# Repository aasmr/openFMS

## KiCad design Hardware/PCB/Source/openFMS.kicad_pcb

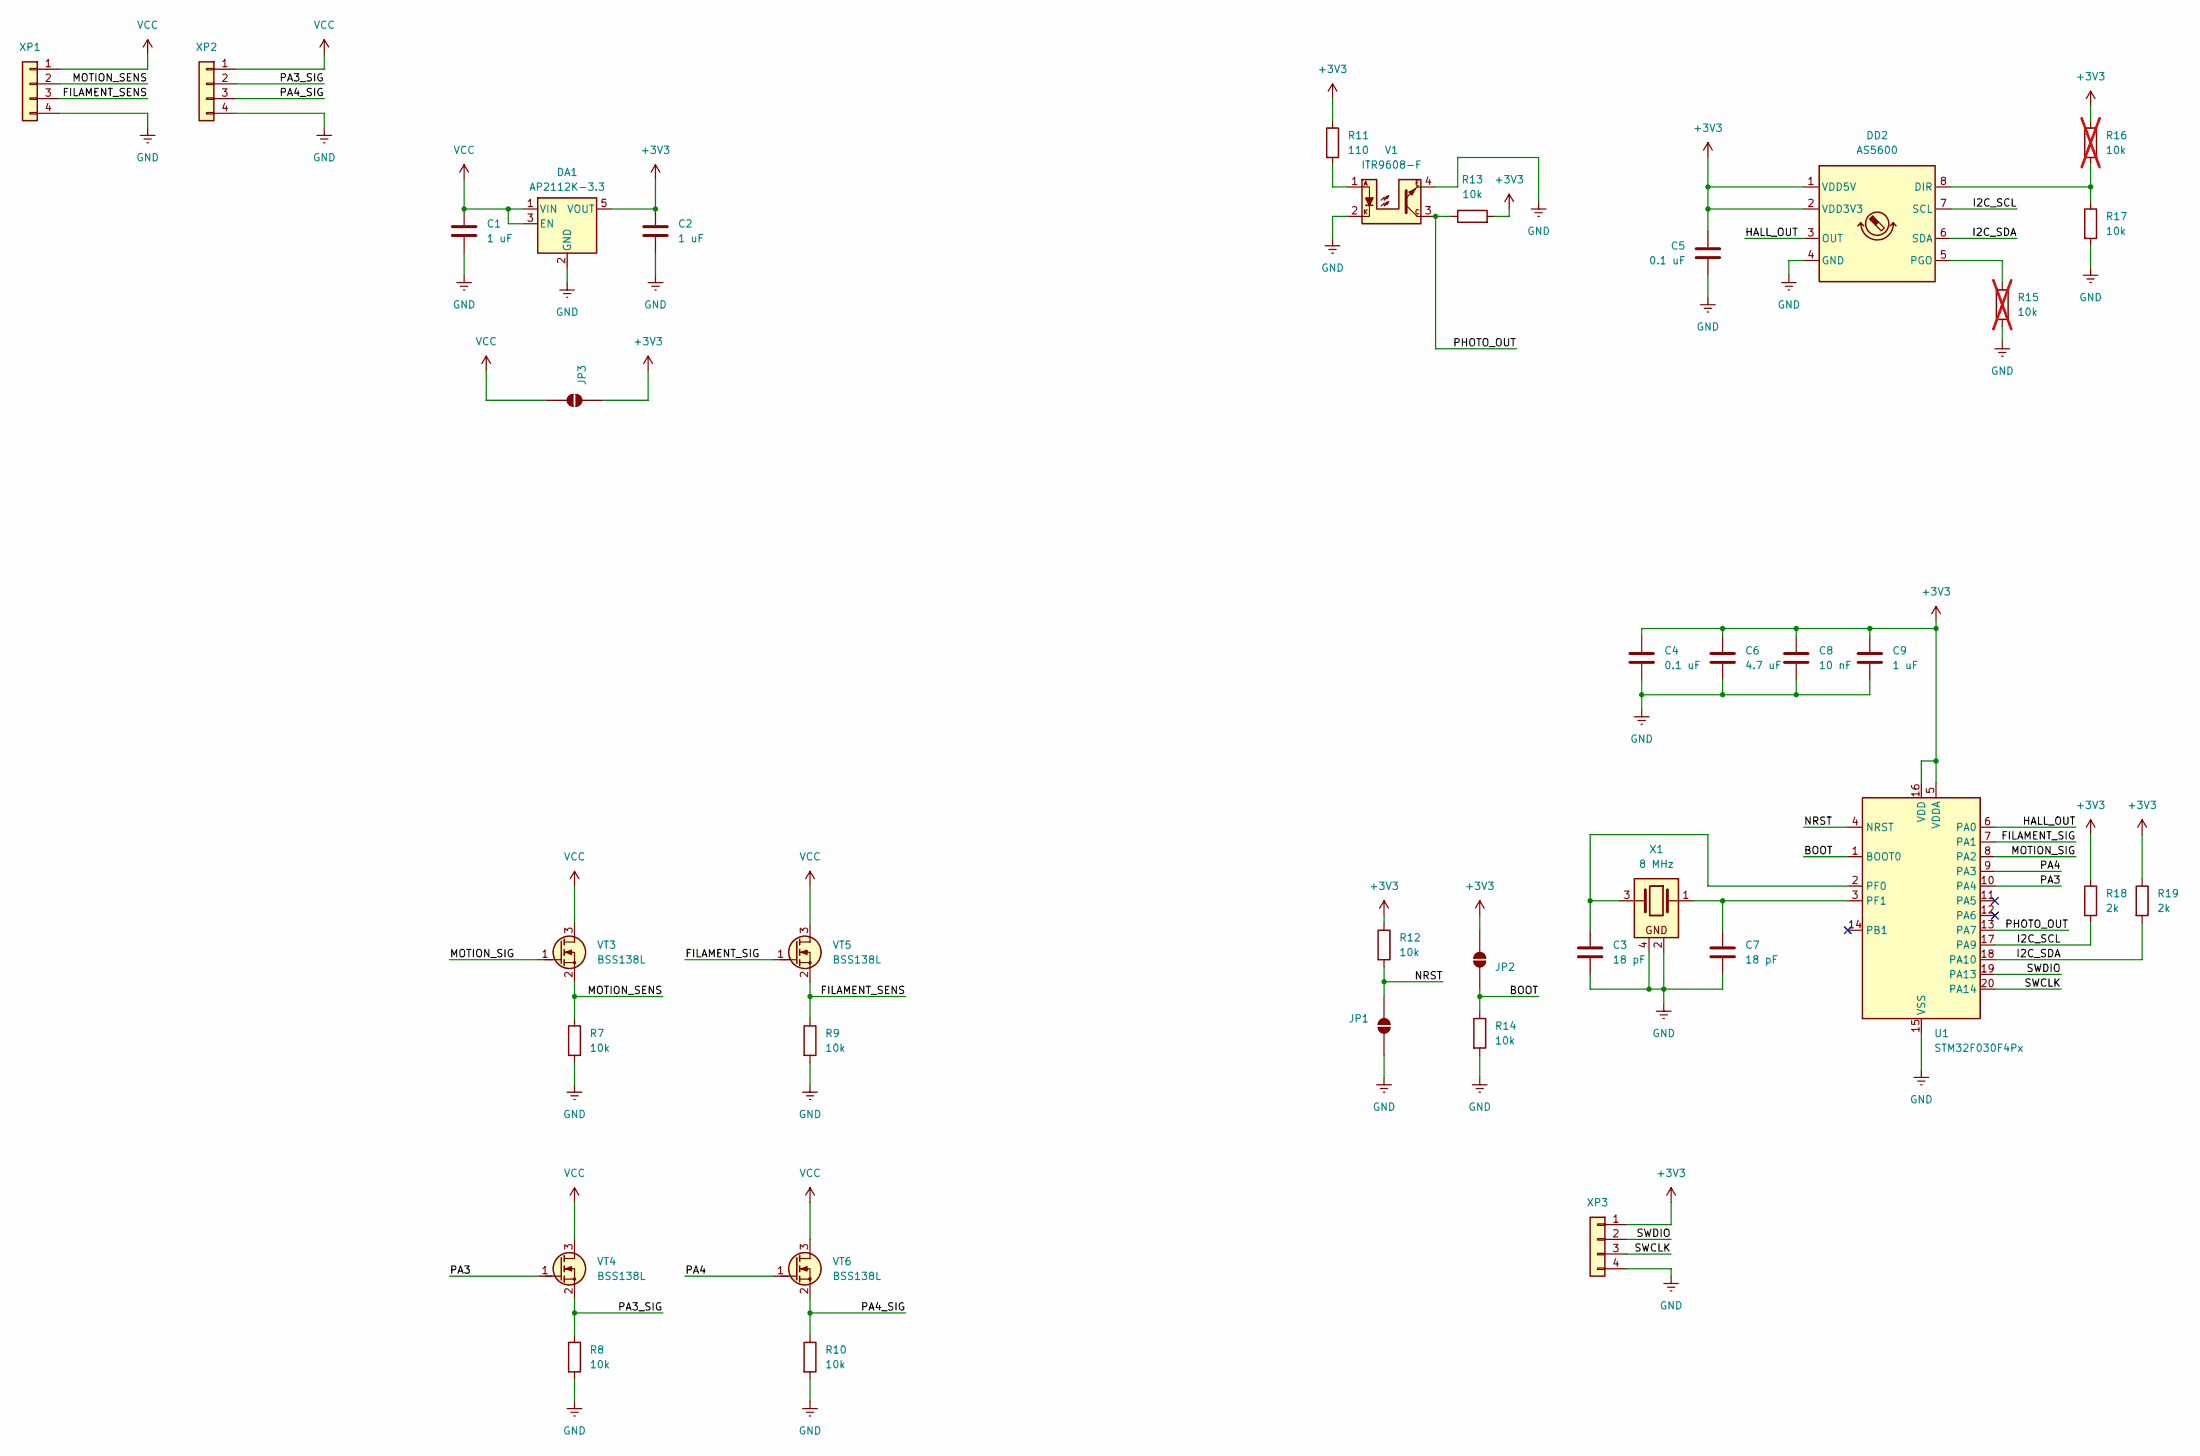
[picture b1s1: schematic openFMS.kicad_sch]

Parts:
C1, C2, C9: 1 uF; C_0603_1608Metric
C3, C7: 18 pF; C_0603_1608Metric
C4, C5: 0.1 uF; C_0603_1608Metric
C6: 4.7 uF; C_0603_1608Metric
C8: 10 nF; C_0603_1608Metric
DA1: AP2112K-3.3; SOT-23-5
DD2: AS5600; SOIC-8_5.3x5.3mm_P1.27mm
JP1, JP2, JP3: SolderJumper_2_Open; SolderJumper-2_P1.3mm_Open_TrianglePad1.0x1.5mm
R7, R8, R9, R10, R12, R13, R14, R17: 10k; R_0603_1608Metric
R11: 110; R_0603_1608Metric
R15, R16: 10k; R_0603_1608Metric; not fitted
R18, R19: 2k; R_0603_1608Metric
U1: STM32F030F4Px; TSSOP-20_4.4x6.5mm_P0.65mm
V1: ITR9608-F; Everlight_ITR9608-F
VT3, VT4, VT5, VT6: BSS138L; SOT-23
X1: 8 MHz; Crystal_SMD_3225-4Pin_3.2x2.5mm; PartNumber DSX321G 8MHZ 12PF 20PPM
XP1, XP2: Conn_01x04; JST_EH_B4B-EH-A_1x04_P2.50mm_Vertical
XP3: Conn_01x04; PinHeader_1x04_P2.54mm_Vertical

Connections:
+3V3: C2.1, C4.1, C5.1, C6.1, C8.1, C9.1, DA1.5 (VOUT), DD2.1 (VDD5V), DD2.2 (VDD3V3), JP2.1 (A), JP3.2 (B), R11.1, R12.1, R13.2, R16.1, R18.1, R19.1, U1.5 (VDDA), U1.16 (VDD), XP3.1
/BOOT: JP2.2 (B), R14.1, U1.1 (BOOT0)
/FILAMENT_SENS: R9.1, VT5.2 (S), XP1.3
/FILAMENT_SIG: U1.7 (PA1), VT5.1 (G)
/HALL_OUT: DD2.3 (OUT), U1.6 (PA0)
/I2C_SCL: DD2.7 (SCL), R18.2, U1.17 (PA9)
/I2C_SDA: DD2.6 (SDA), R19.2, U1.18 (PA10)
/MOTION_SENS: R7.1, VT3.2 (S), XP1.2
/MOTION_SIG: U1.8 (PA2), VT3.1 (G)
/NRST: JP1.2 (B), R12.2, U1.4 (NRST)
/PA3: U1.10 (PA4), VT4.1 (G)
/PA3_SIG: R8.1, VT4.2 (S), XP2.2
/PA4: U1.9 (PA3), VT6.1 (G)
/PA4_SIG: R10.1, VT6.2 (S), XP2.3
/PHOTO_OUT: R13.1, U1.13 (PA7), V1.3
/SWCLK: U1.20 (PA14), XP3.3
/SWDIO: U1.19 (PA13), XP3.2
GND: C1.2, C2.2, C3.2, C4.2, C5.2, C6.2, C7.2, C8.2, C9.2, DA1.2 (GND), DD2.4 (GND), JP1.1 (A), R7.2, R8.2, R9.2, R10.2, R14.2, R15.2, R17.2, U1.15 (VSS), V1.2, V1.4, X1.2, X1.4, XP1.4, XP2.4, XP3.4
unnamed: DD2.8 (DIR), R16.2, R17.1
unnamed: DD2.5 (PGO), R15.1
unnamed: R11.2, V1.1
unnamed: C3.1, U1.2 (PF0), X1.3
unnamed: C7.1, U1.3 (PF1), X1.1
VCC: C1.1, DA1.1 (VIN), DA1.3 (EN), JP3.1 (A), VT3.3 (D), VT4.3 (D), VT5.3 (D), VT6.3 (D), XP1.1, XP2.1

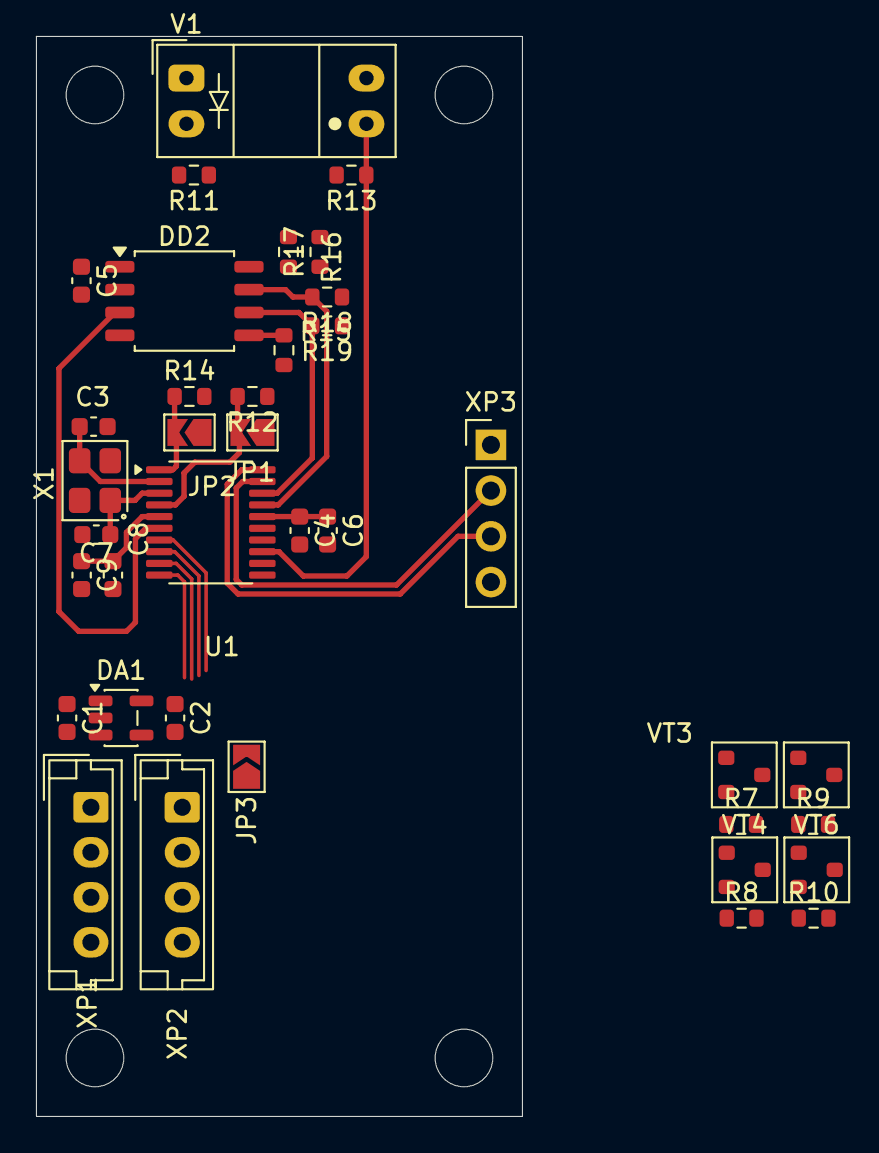
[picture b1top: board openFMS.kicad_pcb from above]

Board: 2 copper layers, 27.0 x 60.0 mm, 37 parts (0 on the bottom side), 24 nets.

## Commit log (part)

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2026-06-09 Add Quartz Resonator to sheme
2026-06-14 Add mechanical CAD files and relocate PCB sources
    Add three FreeCAD mechanical files for the project (encoder_wheel.FCStd, mr52zz.FCStd, openFMS_asm.FCStd) and move KiCad PCB source files from Hardware/Source to Hardware/PCB/Source (openFMS.kicad_pc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
2026-06-15 Add input protection for comparator, spare connector, update crystal load caps
    Added Schottky diodes (BAT54CW) and current‑limiting resistors (10 kΩ) to protect MCP6541 comparator inputs from overvoltage/ESD. Introduced a spare connector wired to unused microcontroller GPIOs fo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
2026-06-15 Edit PCB
2026-06-15 Add TPU ring and update mechanical CAD files
    Add new FreeCAD model 'tpu ring.FCStd' and update existing mechanical FreeCAD files (encoder_wheel.FCStd, mr52zz.FCStd, openFMS_asm.FCStd). These changes reflect revisions to the mechanical designs a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
2026-06-17 WIP: PCB component placement draft + FreeCAD 3D models
    Finished rough component placement on PCB (routing not started). Added draft FreeCAD models for PCB and filament rod to visualize mechanical compatibility.
2026-06-17 WIP: routing
2026-06-26 WIP: routing and mechanical development
